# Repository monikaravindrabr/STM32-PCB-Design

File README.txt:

# STM32 Microcontroller PCB Design

## Overview
Designed a custom two-layer PCB for an STM32 microcontroller using KiCad. This project focuses on schematic design, PCB layout, component placement, routing, and design rule checking.

## Tools Used
- KiCad
- Schematic Editor
- PCB Editor
- KiCad 3D Viewer

## Features
- STM32 microcontroller-based PCB design
- Two-layer PCB layout
- Power supply design and decoupling capacitors
- SWD programming and debugging header
- Component placement and PCB routing
- Design Rule Check (DRC)

## Project Files
- `pcb.kicad_pro` – KiCad project settings
- `pcb.kicad_sch` – Circuit schematic
- `pcb.kicad_pcb` – PCB layout

## Design Workflow
1. Created the circuit schematic.
2. Assigned component footprints.
3. Designed the two-layer PCB layout.
4. Routed electrical connections.
5. Checked design rules and corrected errors.
6. Reviewed the board in the 3D Viewer.

## Author
Monika B R
Electronics and Communication Engineering

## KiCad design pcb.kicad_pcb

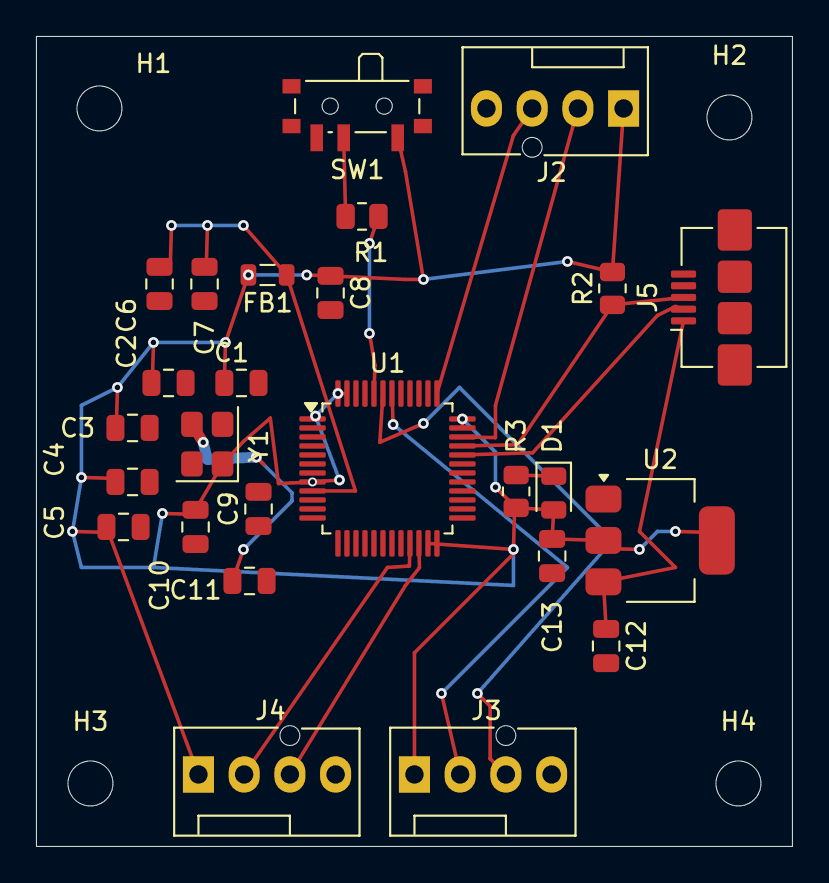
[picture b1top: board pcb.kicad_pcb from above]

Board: 2 copper layers, 42.0 x 45.0 mm, 30 parts (0 on the bottom side), 16 nets.

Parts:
C1, C2, C3, C4, C9: 100n; C_0805_2012Metric
C5: 10u; C_0805_2012Metric
C6: 10n; C_0805_2012Metric
C7, C8: 1u; C_0805_2012Metric
C10, C11: 10p; C_0805_2012Metric
C12, C13: 22u; C_0805_2012Metric
D1: LED; LED_0805_2012Metric
FB1: FerriteBead; L_0805_2012Metric
H1, H2, H3, H4: MountingHole; MountingHole_2.5mm
J2, J3, J4: Conn_01x04_Pin; FanPinHeader_1x04_P2.54mm_Vertical
J5: USB_B_Micro; USB_Micro-B_Amphenol_10104110_Horizontal
R1: 10k; R_0805_2012Metric
R2, R3: 1k5; R_0805_2012Metric
SW1: SW_SPDT; SW_SPDT_PCM12
U1: STM32F103C8Tx; LQFP-48_7x7mm_P0.5mm
U2: AMS1117-3.3; SOT-223-3_TabPin2
Y1: 16Mhz; Crystal_SMD_3225-4Pin_3.2x2.5mm

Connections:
+3.3V: C1.1, C2.1, C3.1, C4.1, C5.1, C8.1, C10.1, C13.1, D1.2 (A), FB1.2, J2.1, J3.1, J4.1, R2.2, R3.2, SW1.1 (A), U1.1 (VBAT), U1.8 (VSSA), U1.23 (VSS), U1.24 (VDD), U1.35 (VSS), U1.36 (VDD), U1.47 (VSS), U1.48 (VDD), U2.2, Y1.1 (1_1)
+3.3VA: C6.1, C7.1, FB1.1, U1.9 (VDDA)
/12 scl: J4.2, U1.21 (PB10)
/12 sda: J4.3 (Pin_4_4), U1.22 (PB11)
/BOOTO: R1.2, U1.44 (BOOT0)
/NRST: C9.1, U1.7 (NRST)
/URX: J3.3, U1.43 (PB7)
/hse out: C11.1, U1.6 (PD1), Y1.3
/swclk: J2.3, U1.37 (PA14)
/swdio: J2.2, U1.34 (PA13)
/usb d+: J5.3 (D+), R2.1, U1.33 (PA12)
/usb d-: J5.2 (D-), U1.32 (PA11)
/utx: J3.2 (Pin_2_2), U1.42 (PB6)
unnamed: D1.1 (K), R3.1
unnamed: R1.1, SW1.2 (B)
VBUS: C12.1, J5.1 (VBUS), U2.3 (VI_3)
